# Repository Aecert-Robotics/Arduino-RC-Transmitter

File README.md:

# Arduino-RC-Transmitter
Arduino Mega Pro powered RC Transmitter using the NRF24L01+ chip

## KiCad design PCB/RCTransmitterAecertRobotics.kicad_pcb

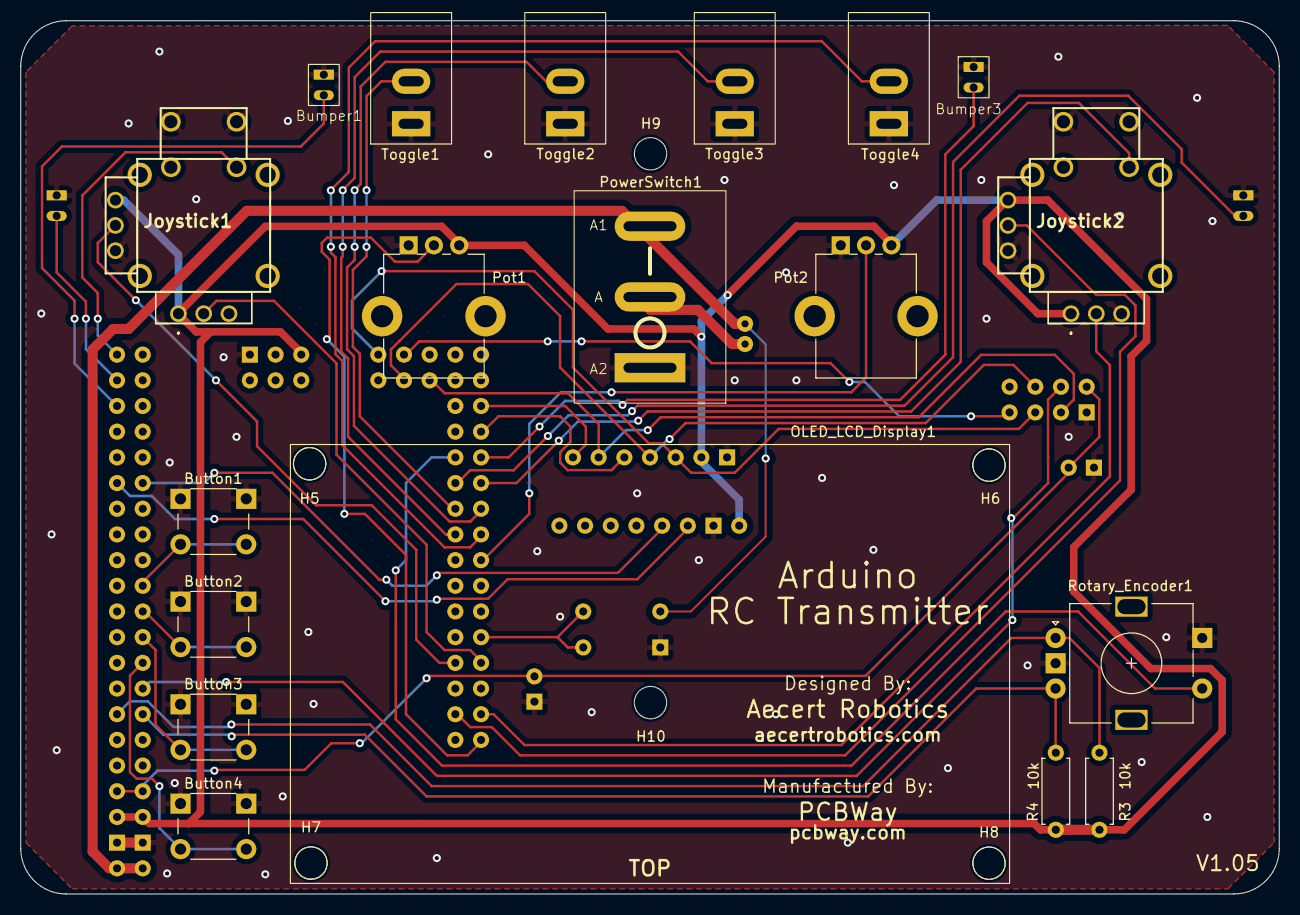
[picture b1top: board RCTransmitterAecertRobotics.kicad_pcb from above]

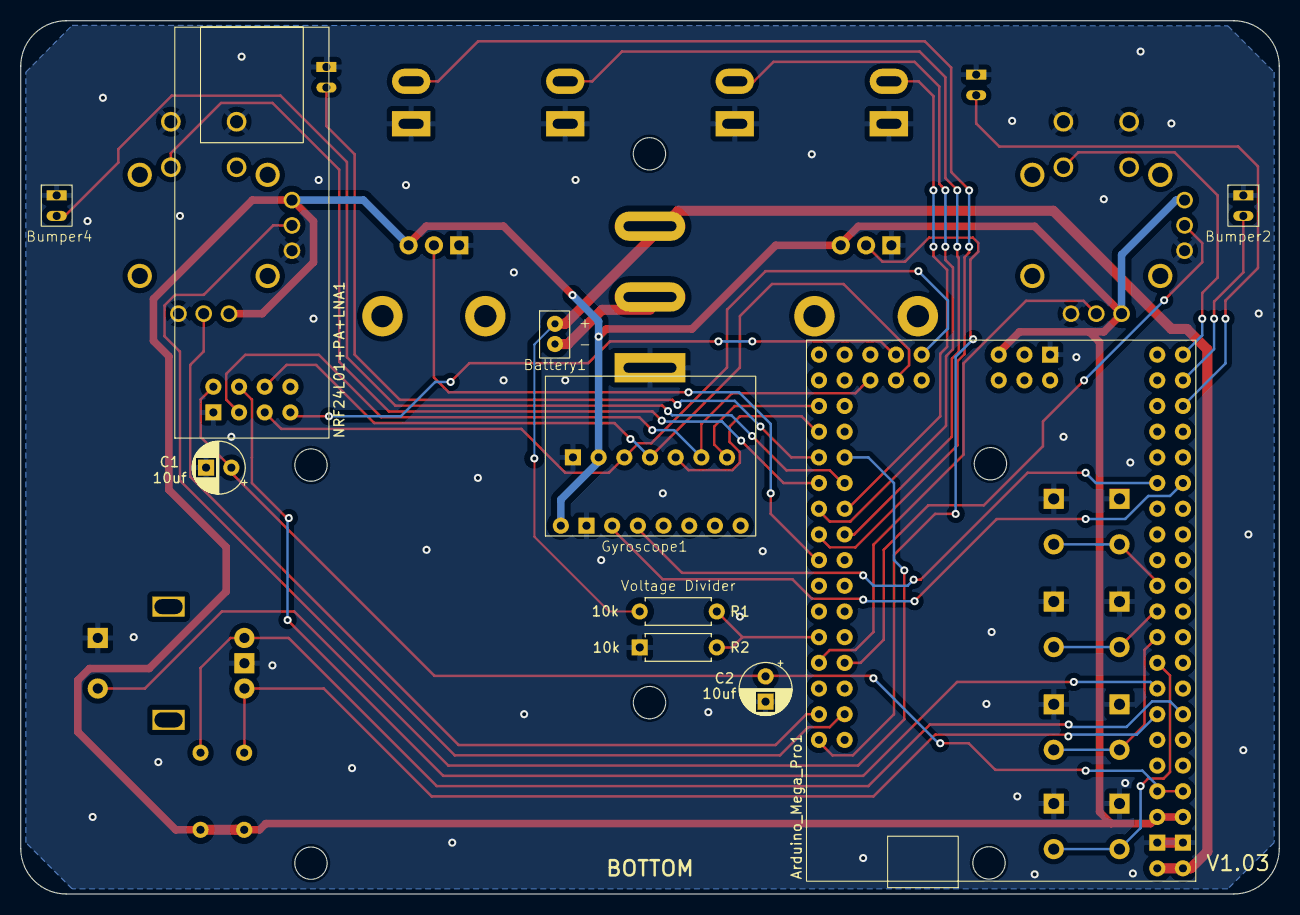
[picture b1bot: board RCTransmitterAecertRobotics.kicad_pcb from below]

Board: 2 copper layers, 124.5 x 86.4 mm, 35 parts (10 on the bottom side), 38 nets.

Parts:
Arduino_Mega_Pro1: Arduino Mega Pro Mini; Arduino Mega Pro
Battery1: 1.27mm_JST_Connector_1; JST Female Connector
Bumper1: SW_Push Left Bumper A; Bumper Pads
Bumper2: SW_Push Left Bumper B; Bumper Pads
Bumper3: SW_Push Right Bumper A; Bumper Pads
Bumper4: SW_Push Right Bumper B; Bumper Pads
Button1: SW_Push A; SW_PUSH_6mm
Button2: SW_Push B; SW_PUSH_6mm
Button3: SW_Push C; SW_PUSH_6mm
Button4: SW_Push D; SW_PUSH_6mm
C1, C2: 10uf; CP_Radial_D5.0mm_P2.50mm
Gyroscope1: MPU6050 Gyroscope
H5, H6, H7, H8, H9, H10: MountingHole_Pad; MountingHole_3.2mm_M3
Joystick1: THB001P Joy Left; THB001P
Joystick2: THB001P Joy Right; THB001P
NRF24L01+PA+LNA1: NRF24L01+PA+LNA1; NRF24L01+ Antenna
OLED_LCD_Display1: SSD1309 2.4inch; OLED LCD Display SSD1309
Pot1, Pot2: 10k; Potentiometer_Bourns_PTV09A-1_Single_Vertical
PowerSwitch1: KCD1 Power Switch; KCD1 Mini Rocker Switch
R1, R2, R3, R4: 10k; R_Axial_DIN0207_L6.3mm_D2.5mm_P7.62mm_Horizontal
Rotary_Encoder1: EC11E; RotaryEncoder_Alps_EC11E-Switch_Vertical_H20mm
Toggle1, Toggle2, Toggle3, Toggle4: SW_DIP_x01; SPST Mini Toggle Switch 2 Pin 2 Position

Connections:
/3.3v: Arduino_Mega_Pro1.3V3, C1.1, C2.1, NRF24L01+PA+LNA1.1 (V+)
/5v: Arduino_Mega_Pro1.5V, Gyroscope1.1 (VCC), Joystick1.1, Joystick1.11 (1'), Joystick2.1, Joystick2.11 (1'), OLED_LCD_Display1.6 (VCC), Pot1.3, Pot2.3, R3.1, R4.1
/Bat+: Arduino_Mega_Pro1.VIN, Battery1.1, PowerSwitch1.3 (Load), R1.2
/Bat-: Battery1.2, PowerSwitch1.2 (Power)
/Battery Voltage: Arduino_Mega_Pro1.A8, R1.1, R2.2
/Button A: Arduino_Mega_Pro1.12 (D12), Button1.2
/Button B: Arduino_Mega_Pro1.10 (D10), Button2.2
/Button C: Arduino_Mega_Pro1.8 (D8), Button3.2
/Button D: Arduino_Mega_Pro1.6 (D6), Button4.2
/CE: Arduino_Mega_Pro1.49 (D49), NRF24L01+PA+LNA1.7 (CE), OLED_LCD_Display1.2 (DC)
/Joy Left Button: Arduino_Mega_Pro1.31 (D31), Joystick1.A1 (COM_1)
/Joy Left X: Arduino_Mega_Pro1.A6, Joystick1.2
/Joy Left Y: Arduino_Mega_Pro1.A7, Joystick1.12 (2')
/Joy Right Button: Arduino_Mega_Pro1.36 (D36), Joystick2.A1 (COM_1)
/Joy Right X: Arduino_Mega_Pro1.A2, Joystick2.2
/Joy Right Y: Arduino_Mega_Pro1.A3, Joystick2.12 (2')
/Left Bumper A: Arduino_Mega_Pro1.27 (D27), Bumper1.2
/Left Bumper B: Arduino_Mega_Pro1.29 (D29), Bumper2.2
/MISO: Arduino_Mega_Pro1.50 (D50(MISO)), NRF24L01+PA+LNA1.5 (MISO)
/MOSI: Arduino_Mega_Pro1.51 (D51(MOSI)), NRF24L01+PA+LNA1.3 (MOSI), OLED_LCD_Display1.4 (SDA)
/NRF CSN: Arduino_Mega_Pro1.4 (D4), NRF24L01+PA+LNA1.2 (CSN)
/Pot Left: Arduino_Mega_Pro1.A0, Pot1.2
/Pot Right: Arduino_Mega_Pro1.A14, Pot2.2
/Right Bumper A: Arduino_Mega_Pro1.38 (D38), Bumper3.2
/Right Bumper B: Arduino_Mega_Pro1.37 (D37), Bumper4.2
/Rotary Encoder Switch: Arduino_Mega_Pro1.39 (D39), Rotary_Encoder1.S1
/RotaryEncoderA: Arduino_Mega_Pro1.2 (D2), R4.2, Rotary_Encoder1.B
/RotaryEncoderB: Arduino_Mega_Pro1.3 (D3), R3.2, Rotary_Encoder1.A
/SCK: Arduino_Mega_Pro1.52 (D52(SCLK)), NRF24L01+PA+LNA1.6 (SCK), OLED_LCD_Display1.5 (SCK)
/SCL: Arduino_Mega_Pro1.21 (D21(SCL)), Gyroscope1.3 (SCL)
/SDA: Arduino_Mega_Pro1.20 (D20(SDA)), Gyroscope1.4 (SDA)
/Screen CS: Arduino_Mega_Pro1.42 (D42), OLED_LCD_Display1.1 (CS)
/Screen RES: Arduino_Mega_Pro1.40 (D40), OLED_LCD_Display1.3 (RES)
/Toggle A: Arduino_Mega_Pro1.35 (D35), Toggle1.2
/Toggle B: Arduino_Mega_Pro1.34 (D34), Toggle2.2
/Toggle C: Arduino_Mega_Pro1.33 (D33), Toggle3.2
/Toggle D: Arduino_Mega_Pro1.32 (D32), Toggle4.2
GND: Arduino_Mega_Pro1.GND, Bumper1.1, Bumper2.1, Bumper3.1, Bumper4.1, Button1.1, Button2.1, Button3.1, Button4.1, C1.2, C2.2, Gyroscope1.2 (GND), Joystick1.3, Joystick1.13 (3'), Joystick1.C1 (NO_1), Joystick1.D1 (NO_2), Joystick2.3, Joystick2.13 (3'), Joystick2.C1 (NO_1), Joystick2.D1 (NO_2), NRF24L01+PA+LNA1.8 (GND), OLED_LCD_Display1.7 (GND), Pot1.1, Pot2.1, PowerSwitch1.1 (LED), R2.1, Rotary_Encoder1.C, Rotary_Encoder1.S2, Toggle1.1, Toggle2.1, Toggle3.1, Toggle4.1

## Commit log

2024-11-24 Added godot mockup
2024-11-24 updated pcb
2024-11-24 pcb update
2024-11-24 updated pcb, created gerber
2024-11-28 added springs to case plate
2024-11-30 letters
2024-12-03 stl updates
2024-12-10 fixes to fit the new parts
2025-01-06 Refactored code to fix a bug related to rotary encoder pressing
2025-01-16 Simple Transmitter + Receiver code
2025-01-30 added receiver example
2025-01-30 refactoring
2025-01-31 added settings examples
2025-02-04 updated STL groups
2025-02-10 Updated PCB to fix bumper plug clearance
2025-02-10 updated kicad project
2025-02-15 updated case bottom
2025-02-15 refactor
2025-02-17 new pics
2025-02-21 added a battery percentage display using the data from the voltage divider
2025-02-26 stl groups
2025-02-27 pics
2025-02-27 plate names
2025-03-11 code no longer freezes if gyro doesnt work.
2025-03-11 setup printing
2025-03-11 debug prints
2025-03-18 stls
2025-04-06 updated code to work with the new hexapod code
2025-04-06 reworked joystick caps to not require glue
2025-04-21 added gyro data to data package and gyro mode to homepage
2025-04-22 gyro data fixed.
    the mpu5060_light library that i use has a -30 - 30 degree limit. i now enforce that.
